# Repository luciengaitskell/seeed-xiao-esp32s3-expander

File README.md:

# seeed-xiao-esp32s3-expander
An expansion board for the Seeed Studio XIAO ESP32-S3 (Plus) using the B2B connector

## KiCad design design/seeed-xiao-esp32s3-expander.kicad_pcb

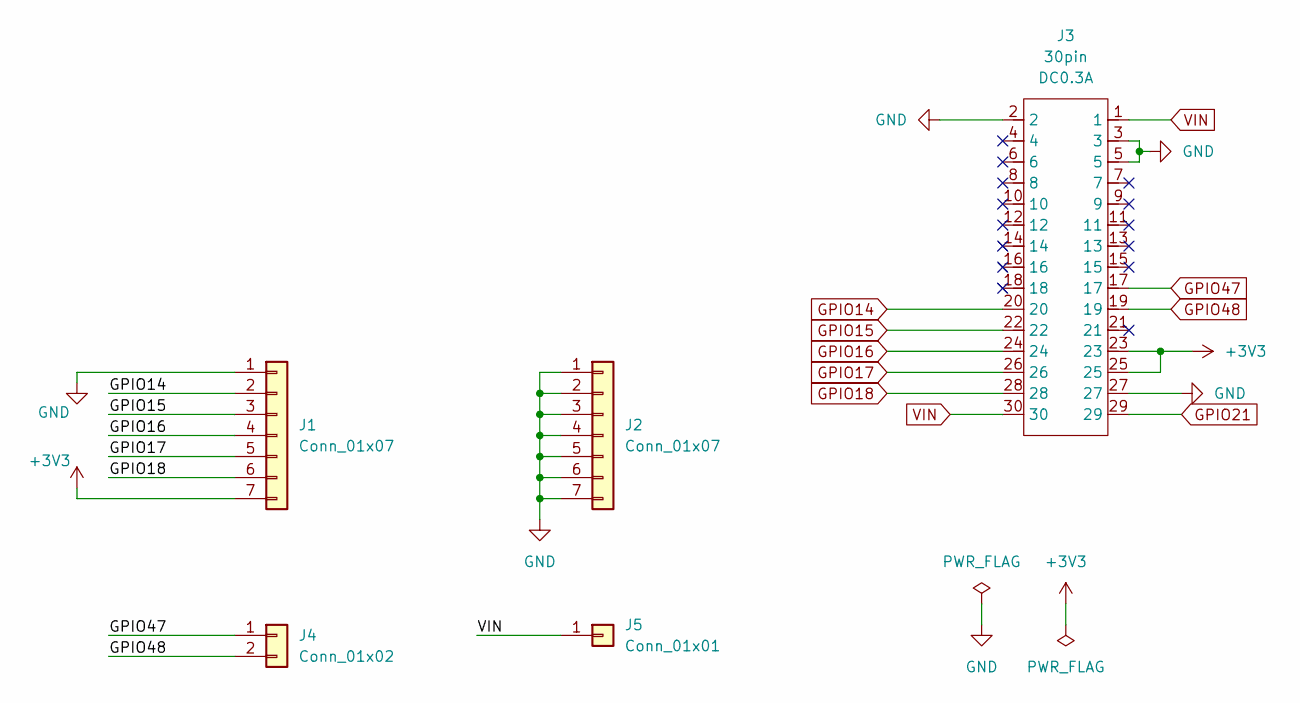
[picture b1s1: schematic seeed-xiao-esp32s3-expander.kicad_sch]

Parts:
J1, J2: Conn_01x07; PinHeader_1x07_P2.54mm
J3: 30pin; BTB2X15-FEMALE-8.6X2.94X3.9MM; Rating DC0.3A; MPN BTB SCOKET P0.40
J4: Conn_01x02; PinHeader_1x02_P2.54mm_Vertical
J5: Conn_01x01; PinHeader_1x01_P2.54mm_Vertical

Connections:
+3V3: J1.7, J3.23, J3.25
GND: J1.1, J2.1, J2.2, J2.3, J2.4, J2.5, J2.6, J2.7, J3.2, J3.3, J3.5, J3.27
GPIO14: J1.2, J3.20
GPIO15: J1.3, J3.22
GPIO16: J1.4, J3.24
GPIO17: J1.5, J3.26
GPIO18: J1.6, J3.28
GPIO21: J3.29
GPIO47: J3.17, J4.1
GPIO48: J3.19, J4.2
VIN: J3.1, J3.30, J5.1 (Pin_1_1)

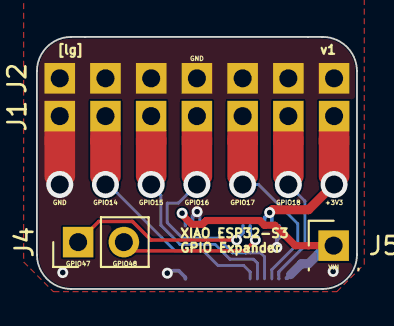
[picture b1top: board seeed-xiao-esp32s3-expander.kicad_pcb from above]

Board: 2 copper layers, 17.8 x 14.0 mm, 12 parts (1 on the bottom side), 10 nets.

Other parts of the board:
+3V3: SolderPad_1x01_SMD
GND: SolderPad_1x01_SMD
GPIO14, GPIO15, GPIO16, GPIO17, GPIO18: SolderPad_1x01_SMD

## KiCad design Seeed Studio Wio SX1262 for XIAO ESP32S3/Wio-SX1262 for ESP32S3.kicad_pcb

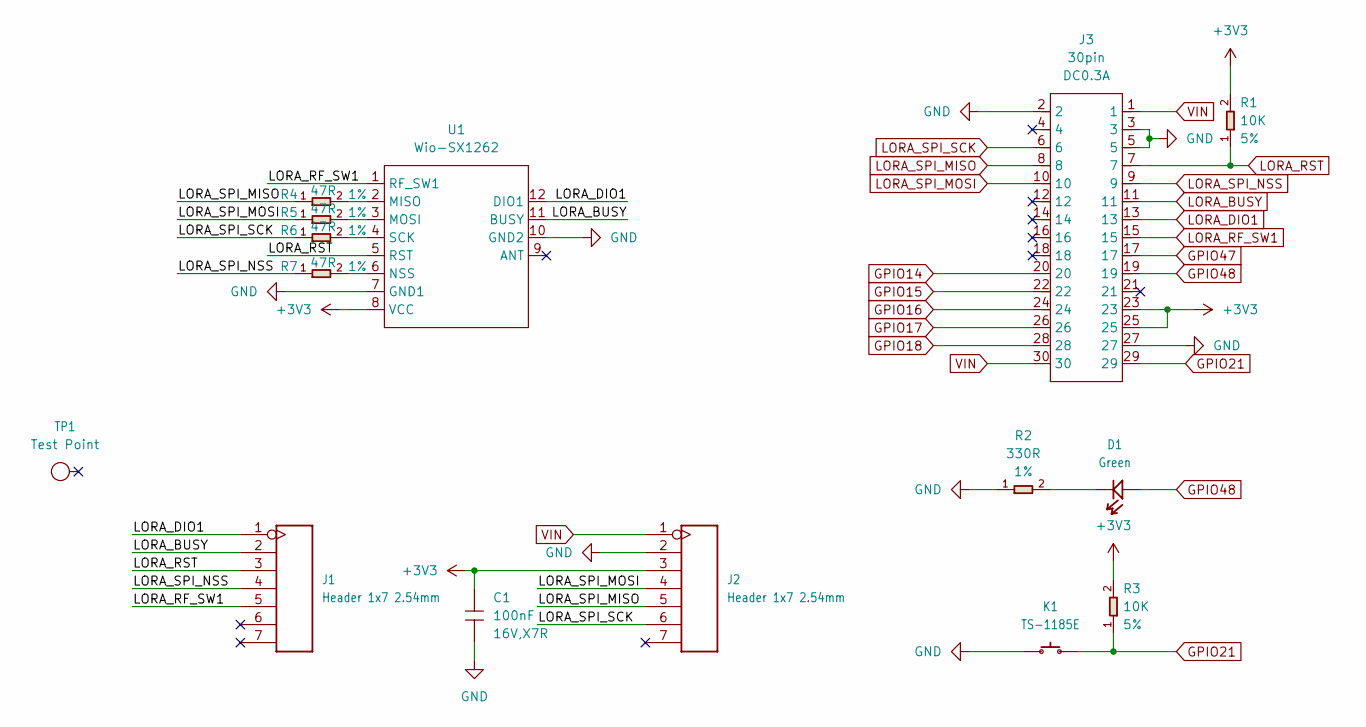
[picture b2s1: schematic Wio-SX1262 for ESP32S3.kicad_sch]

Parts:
C1: 100nF; C0402; Voltage Rating 16V,X7R; MPN CC0402KRX7R7BB104
D1: Green; LED-0603; MPN 19-217/G7C-AN1P2/3T
J1, J2: Header 1x7 2.54mm; H7-2.54; Part Type Header
J3: 30pin; BTB2X15-FEMALE-8.6X2.94X3.9MM; Rating DC0.3A; MPN BTB SCOKET P0.40
K1: TS-1185E; BUTTON2P_3_9X3X2MM; MPN TS-1185E
R1, R3: 10K; R0402; Power Rating 5%; MPN RC0402JR-0710KL
R2: 330R; R0402; Power Rating 1%; MPN RC0402FR-07330RL
R4, R5, R6, R7: 47R; R0402; Power Rating 1%; MPN RC0201FR-0745RL
TP1: Test Point; TP-D3_5c2_2mm; Part Type Test Point
U1: Wio-SX1262; MODULE12P-1.27-11X11.6MM; MPN Wio-SX1262

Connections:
+3V3: C1.1, J2.3, J3.23, J3.25, R1.2, R3.2, U1.8 (VCC)
GND: C1.2, J2.2, J3.2, J3.3, J3.5, J3.27, K1.1, R2.1, U1.7 (GND1), U1.10 (GND2)
GPIO14: J3.20
GPIO15: J3.22
GPIO16: J3.24
GPIO17: J3.26
GPIO18: J3.28
GPIO21: J3.29, K1.2, R3.1
GPIO47: J3.17
GPIO48: D1.1 (+), J3.19
LORA_BUSY: J1.2, J3.11, U1.11 (BUSY)
LORA_DIO1: J1.1, J3.13, U1.12 (DIO1)
LORA_RF_SW1: J1.5, J3.15, U1.1 (RF_SW1)
LORA_RST: J1.3, J3.7, R1.1, U1.5 (RST)
LORA_SPI_MISO: J2.5, J3.8, R4.1
LORA_SPI_MOSI: J2.4, J3.10, R5.1
LORA_SPI_NSS: J1.4, J3.9, R7.1
LORA_SPI_SCK: J2.6, J3.6, R6.1
unnamed: D1.2 (-), R2.2
unnamed: R4.2, U1.2 (MISO)
unnamed: R5.2, U1.3 (MOSI)
unnamed: R7.2, U1.6 (NSS)
unnamed: R6.2, U1.4 (SCK)
VIN: J2.1, J3.1, J3.30

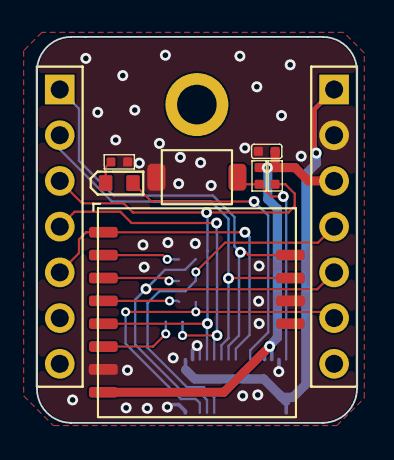
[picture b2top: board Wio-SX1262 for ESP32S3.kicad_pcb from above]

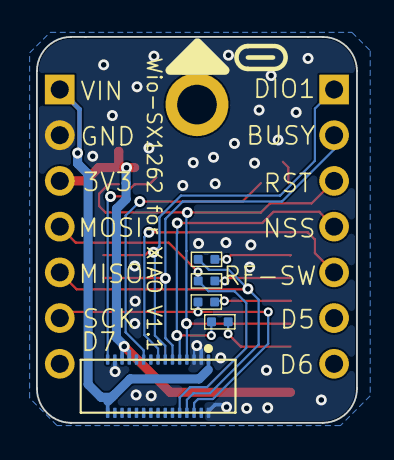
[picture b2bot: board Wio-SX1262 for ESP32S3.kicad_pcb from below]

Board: 2 copper layers, 17.8 x 21.4 mm, 15 parts (5 on the bottom side), 18 nets.
